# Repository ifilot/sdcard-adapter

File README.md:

# SD-CARD Development Board

This development board simplifies interfacing with SD cards by translating 5V logic signals to 3.3V signals, making it ideal for projects using microcontrollers or systems with 5V logic levels. 

## Features
- 5V to 3.3V signal level translation
- Compatible with standard SD cards

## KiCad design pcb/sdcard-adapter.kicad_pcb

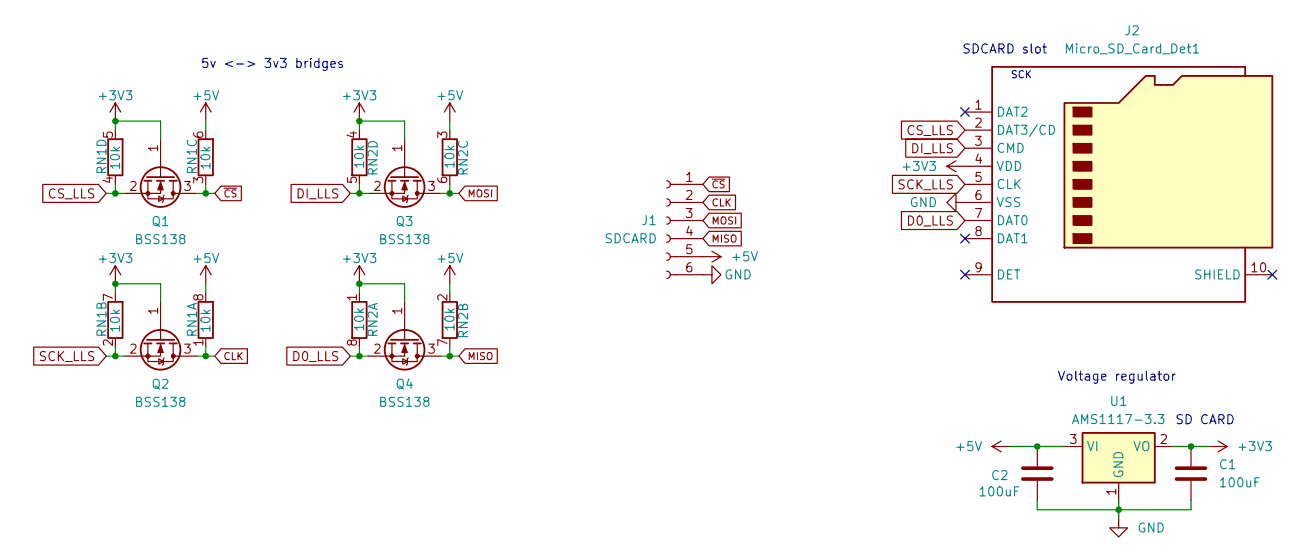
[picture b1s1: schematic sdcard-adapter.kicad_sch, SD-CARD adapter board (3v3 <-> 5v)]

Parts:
C1, C2: 100uF; C_1206_3216Metric_Pad1.33x1.80mm_HandSolder; LCSC Part # C309030
J1: SDCARD; PinHeader_1x06_P2.54mm_Vertical
J2: Micro_SD_Card_Det1; sdcard-socket; LCSC Part # C381082
Q1, Q2, Q3, Q4: BSS138; SOT-23; LCSC C78284
RN1, RN2: 10k; R_Array_Convex_4x0603; LCSC C110924
U1: AMS1117-3.3; SOT-223-3_TabPin2; LCSC Part # C5346136

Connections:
+3V3: C1.1, J2.4 (VDD), Q1.1 (G), Q2.1 (G), Q3.1 (G), Q4.1 (G), RN1.5 (R4.2), RN1.7 (R2.2), RN2.1 (R1.1), RN2.4 (R4.1), U1.2 (VO)
+5V: C2.1, J1.5, RN1.6 (R3.2), RN1.8 (R1.2), RN2.2 (R2.1), RN2.3 (R3.1), U1.3 (VI)
CLK: J1.2, Q2.3 (D), RN1.1 (R1.1)
CS_LLS: J2.2 (DAT3/CD), Q1.2 (S), RN1.4 (R4.1)
D0_LLS: J2.7 (DAT0), Q4.2 (S), RN2.8 (R1.2)
DI_LLS: J2.3 (CMD), Q3.2 (S), RN2.5 (R4.2)
GND: C1.2, C2.2, J1.6, J2.6 (VSS), U1.1 (GND)
MISO: J1.4, Q4.3 (D), RN2.7 (R2.2)
MOSI: J1.3, Q3.3 (D), RN2.6 (R3.2)
SCK_LLS: J2.5 (CLK), Q2.2 (S), RN1.2 (R2.1)
~CS: J1.1, Q1.3 (D), RN1.3 (R3.1)

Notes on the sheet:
SDCARD slot
SD CARD
5v <-> 3v3 bridges
Voltage regulator
SCK

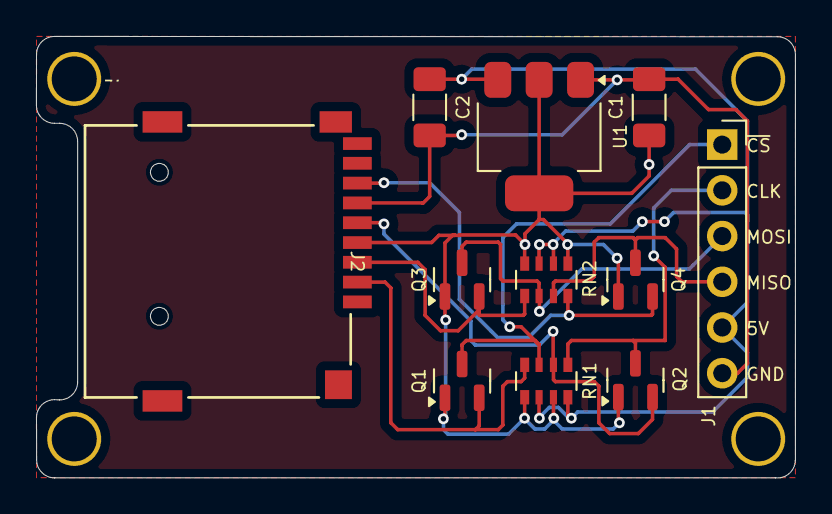
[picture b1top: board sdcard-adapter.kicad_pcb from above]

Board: 2 copper layers, 42.2 x 24.5 mm, 11 parts (0 on the bottom side), 11 nets.

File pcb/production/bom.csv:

Designator,Footprint,Quantity,Value,LCSC Part #
"C1, C2",1206,2,100uF,C309030
J1,sdcard-socket,1,SDCARD,
J2,CONN9_MSD-1_CUD,1,Micro_SD_Card_Det1,C381082
"Q1, Q2, Q3, Q4",SOT-23,4,BSS138,C78284
"RN1, RN2",R_Array_Convex_4x0603,2,10k,C110924
U1,SOT-223-3_TabPin2,1,AMS1117-3.3,C5346136

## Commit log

2025-01-25 Adding README.md
2025-05-10 Adding step files
